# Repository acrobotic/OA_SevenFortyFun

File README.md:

## Ai\_Synth\_AVR

PCB design files (EAGLE) for a transistor-scale version of the μA741 Op-Amp
Integrated Circuit.

## Description

For more details, check out the product page at:

   * https://acrobotic.com/acr-00003

Designed by ACROBOTIC Industries in collaboration with Shane Petcavich.  
Please consider buying products from us to help fund future Open-Source 
projects like this! We’ll always put our best effort in every project, and 
release all our design files and code for you to use. 

## License

Released under the Creative Commons Attribution, Share-Alike license. Please 
check LICENSE.txt for more information. All text above must be included in any 
redistribution.

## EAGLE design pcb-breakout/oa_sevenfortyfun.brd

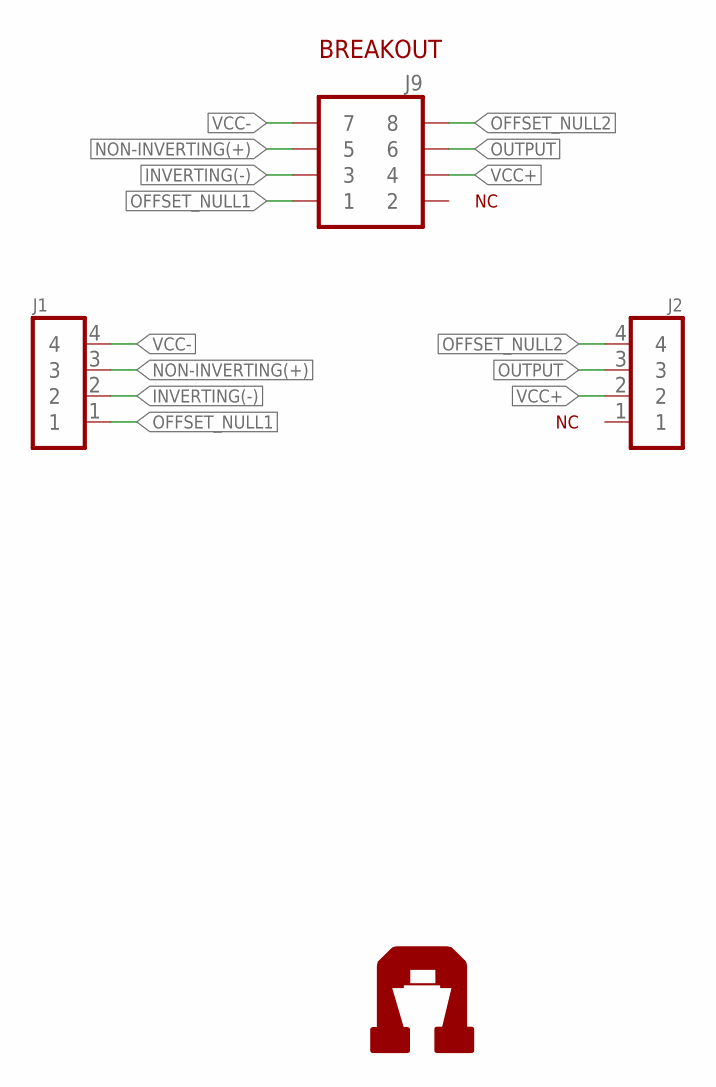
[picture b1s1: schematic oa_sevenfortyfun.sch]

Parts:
J1: 1X04NOSILK; 1X04-NOSILK
J2: 1X04NOFIRST; 1X04-NOFIRST
J9: 2X04SHR; 2X04-SHR
U$3: AI-LOGOXS; AI-LOGO-XS

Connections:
INVERTING(-): J1.2, J9.3
NON-INVERTING(+): J1.3, J9.5
OFFSET_NULL1: J1.1, J9.1
OFFSET_NULL2: J2.4, J9.8
OUTPUT: J2.3, J9.6
VCC+: J2.2, J9.4
VCC-: J1.4, J9.7

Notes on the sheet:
BREAKOUT

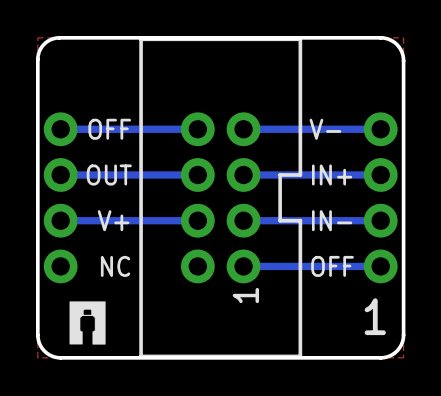
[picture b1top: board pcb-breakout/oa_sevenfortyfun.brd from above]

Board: 2 copper layers, 20.3 x 17.8 mm, 4 parts (0 on the bottom side), 7 nets.

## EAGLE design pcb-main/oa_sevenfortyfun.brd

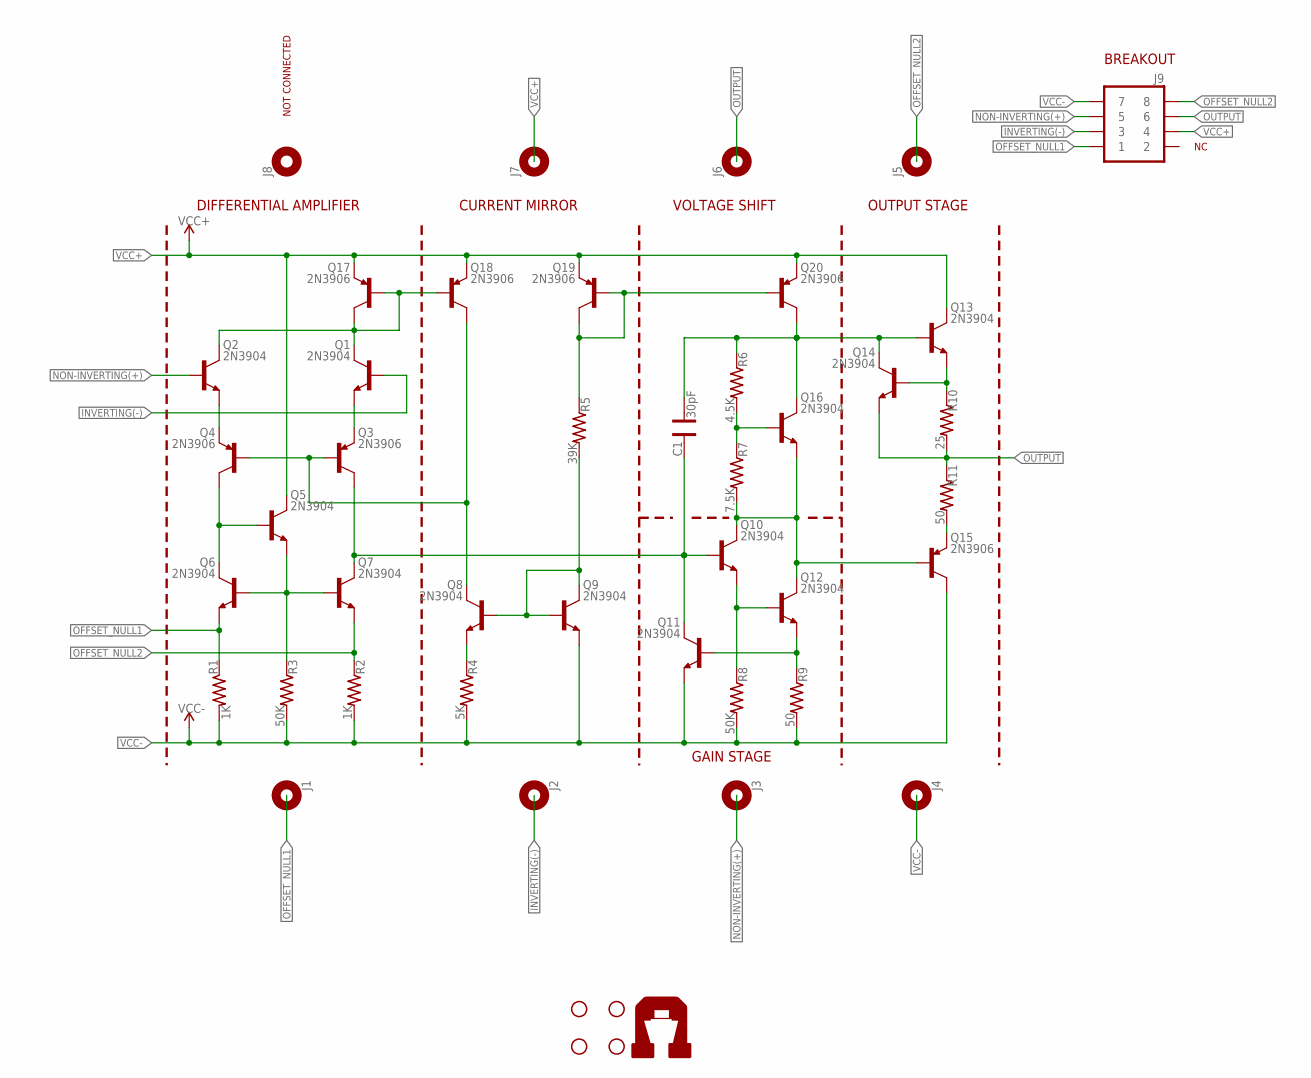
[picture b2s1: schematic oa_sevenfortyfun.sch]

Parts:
C1: 30pF; CAP-025X050
J1, J2, J3, J4, J5, J6, J7, J8: 1X01-TERM
J9: 2X04SHR; 2X04-SHR
Q1, Q2, Q5, Q6, Q7, Q8, Q9, Q10, Q11, Q12, Q13, Q14, Q16: 2N3904; TO-92-NPN
Q3, Q4, Q15, Q17, Q18, Q19, Q20: 2N3906; TO-92-PNP
R1, R2: 1K; RES-AXIAL-0.4
R3, R8: 50K; RES-AXIAL-0.4
R4: 5K; RES-AXIAL-0.4
R5: 39K; RES-AXIAL-0.4
R6: 4.5K; RES-AXIAL-0.4
R7: 7.5K; RES-AXIAL-0.4
R9, R11: 50; RES-AXIAL-0.4
R10: 25; RES-AXIAL-0.4
STANDOFF1, STANDOFF2, STANDOFF3, STANDOFF4: STAND-OFF4; STAND-OFF-4
U$3: AI-LOGOL; AI-LOGO-L

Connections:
INVERTING(-): J2.1, J9.3, Q1.2 (B)
unnamed: Q1.3 (C), Q2.3 (C), Q17.1 (C), Q17.2 (B), Q18.2 (B)
unnamed: Q2.1 (E), Q4.3 (E)
unnamed: Q1.1 (E), Q3.3 (E)
unnamed: Q4.1 (C), Q5.2 (B), Q6.3 (C)
unnamed: C1.2, Q3.1 (C), Q7.3 (C), Q10.2 (B), Q11.3 (C)
unnamed: Q5.1 (E), Q6.2 (B), Q7.2 (B), R3.P$1 (1)
unnamed: Q15.3 (E), R11.P$2 (2)
unnamed: Q3.2 (B), Q4.2 (B), Q8.3 (C), Q18.1 (C)
unnamed: Q8.1 (E), R4.P$1 (1)
unnamed: Q10.1 (E), Q12.2 (B), R8.P$1 (1)
unnamed: Q19.1 (C), Q19.2 (B), Q20.2 (B), R5.P$1 (1)
unnamed: Q8.2 (B), Q9.2 (B), Q9.3 (C), R5.P$2 (2)
unnamed: Q10.3 (C), Q12.3 (C), Q15.2 (B), Q16.1 (E), R7.P$2 (2)
unnamed: Q16.2 (B), R6.P$2 (2), R7.P$1 (1)
unnamed: Q11.2 (B), Q12.1 (E), R9.P$1 (1)
unnamed: C1.1, Q13.2 (B), Q14.3 (C), Q16.3 (C), Q20.1 (C), R6.P$1 (1)
unnamed: Q13.1 (E), Q14.2 (B), R10.P$1 (1)
NON-INVERTING(+): J3.1, J9.5, Q2.2 (B)
OFFSET_NULL1: J1.1, J9.1, Q6.1 (E), R1.P$1 (1)
OFFSET_NULL2: J5.1, J9.8, Q7.1 (E), R2.P$1 (1)
OUTPUT: J6.1, J9.6, Q14.1 (E), R10.P$2 (2), R11.P$1 (1)
VCC+: J7.1, J9.4, Q5.3 (C), Q13.3 (C), Q17.3 (E), Q18.3 (E), Q19.3 (E), Q20.3 (E)
VCC-: J4.1, J9.7, Q9.1 (E), Q11.1 (E), Q15.1 (C), R1.P$2 (2), R2.P$2 (2), R3.P$2 (2), R4.P$2 (2), R8.P$2 (2), R9.P$2 (2)

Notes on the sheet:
DIFFERENTIAL AMPLIFIER
CURRENT MIRROR
VOLTAGE SHIFT
OUTPUT STAGE
BREAKOUT
NOT CONNECTED
GAIN STAGE

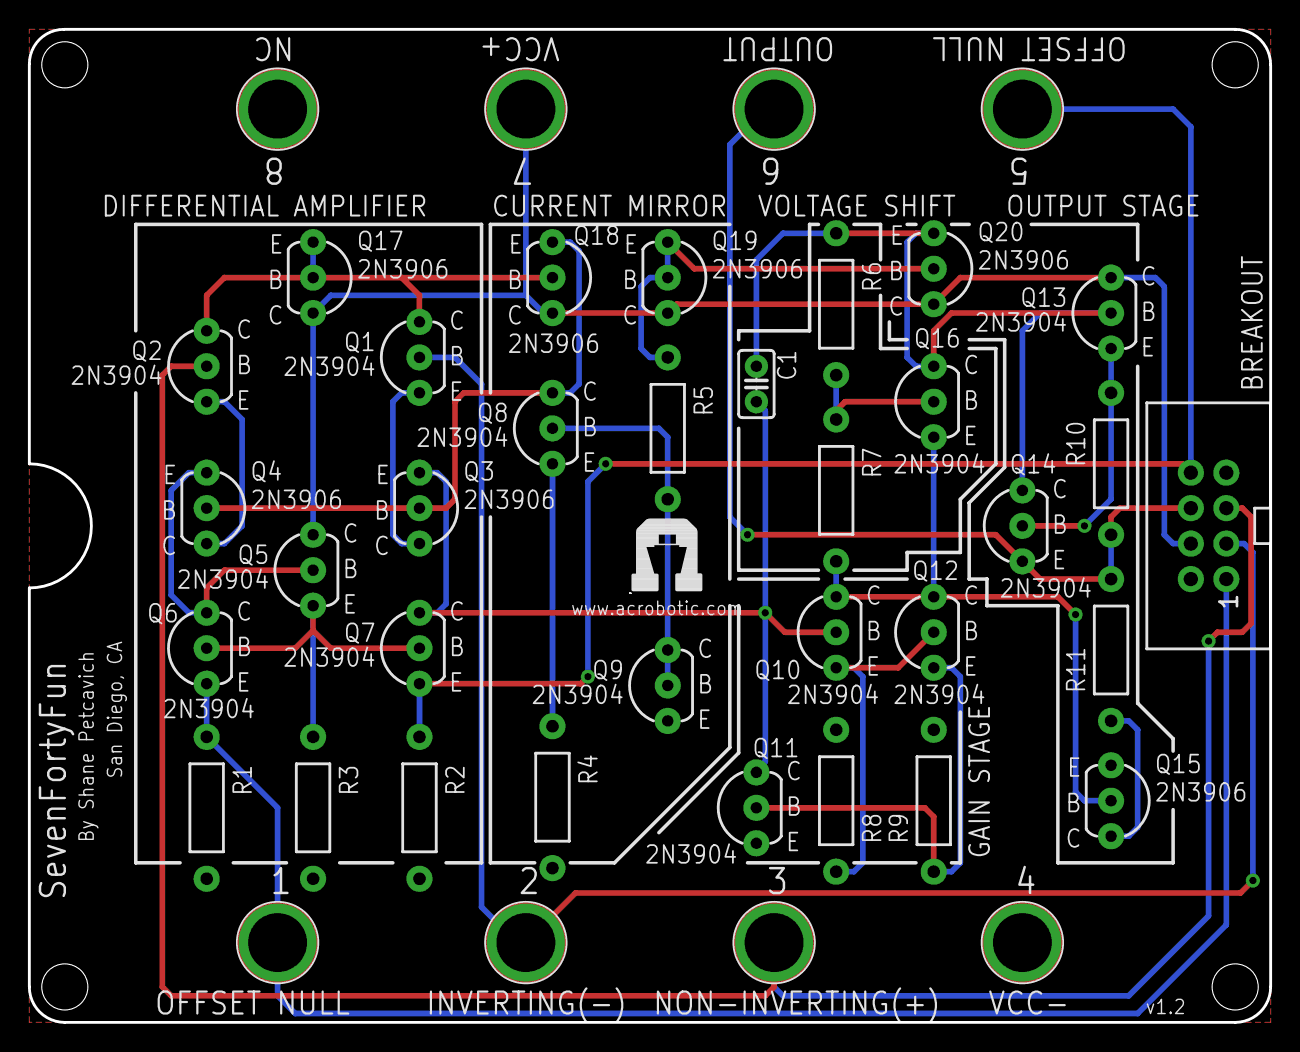
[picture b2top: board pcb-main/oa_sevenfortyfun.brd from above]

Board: 2 copper layers, 88.9 x 71.1 mm, 46 parts (0 on the bottom side), 24 nets.

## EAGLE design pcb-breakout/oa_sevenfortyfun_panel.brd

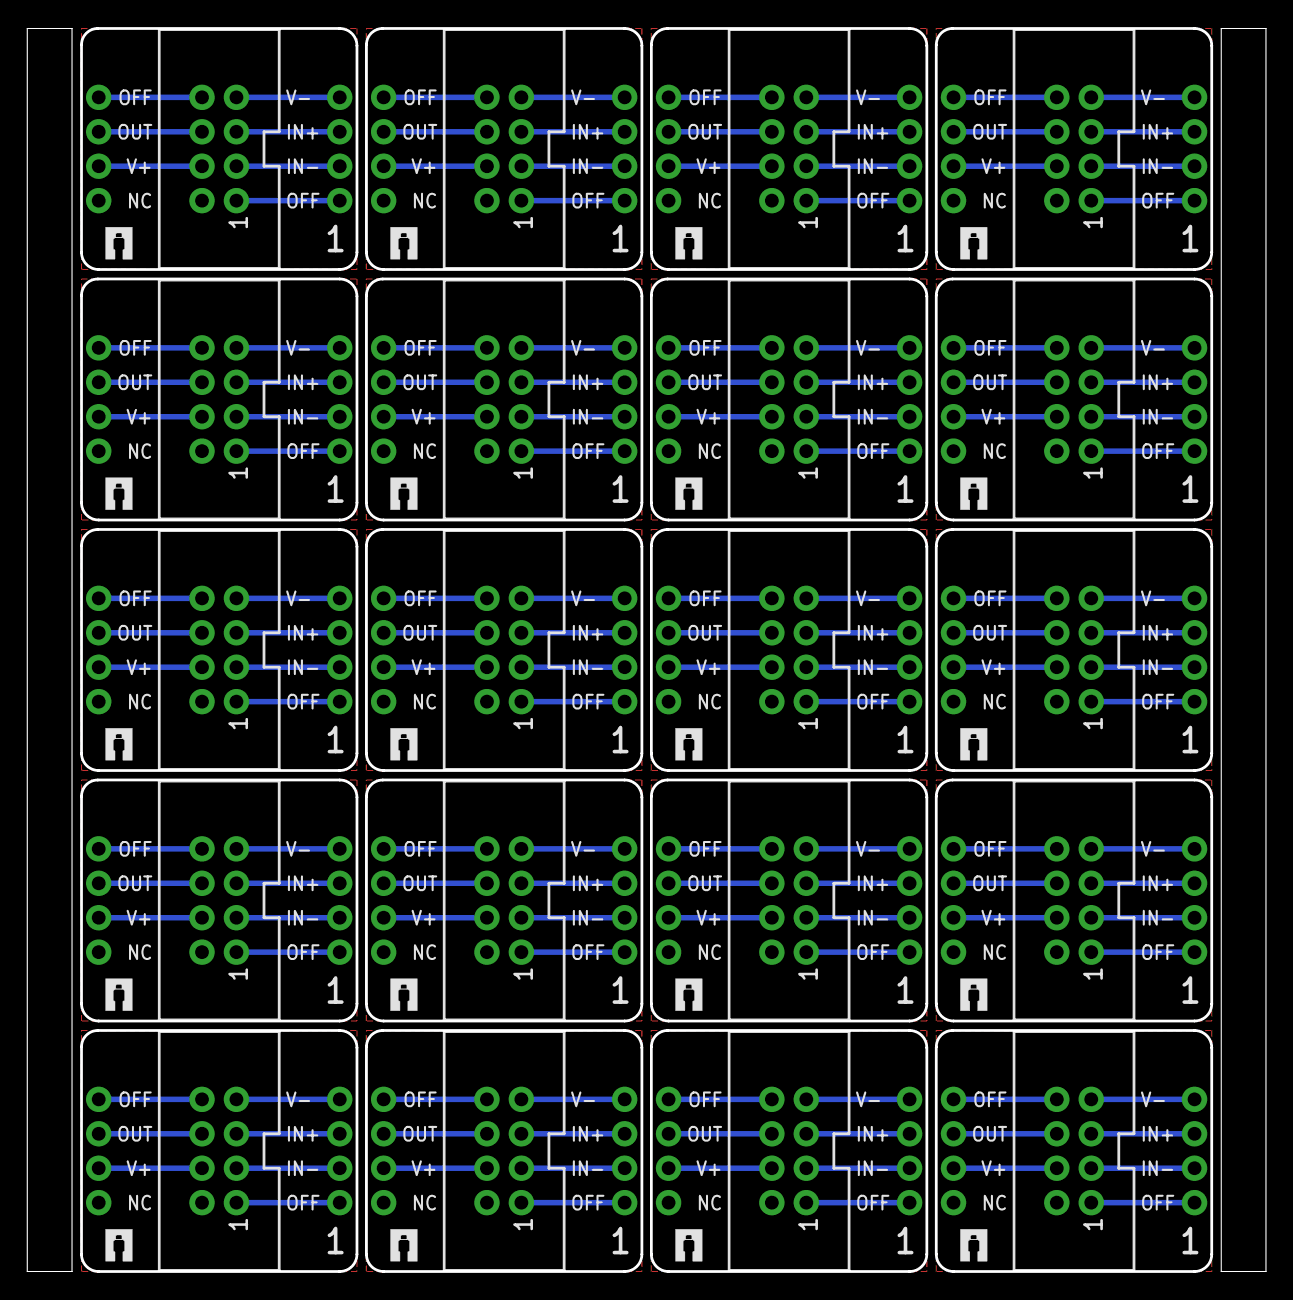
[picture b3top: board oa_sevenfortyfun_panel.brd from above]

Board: 2 copper layers, 91.2 x 91.7 mm, 80 parts (0 on the bottom side), 140 nets.

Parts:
J1, J4, J7, J11, J14, J17, J20, J23, J26, J29, J32, J35, J38, J41, J44, J47, J50, J53, J56, J59: 1X04NOSILK; 1X04-NOSILK
J2, J5, J8, J12, J15, J18, J21, J24, J27, J30, J33, J36, J39, J42, J45, J48, J51, J54, J57, J60: 1X04NOFIRST; 1X04-NOFIRST
J3, J6, J9, J10, J13, J16, J19, J22, J25, J28, J31, J34, J37, J40, J43, J46, J49, J52, J55, J58: 2X04SHR; 2X04-SHR
U$1, U$2, U$3, U$4, U$5, U$6, U$7, U$8, U$9, U$10, U$11, U$12, U$13, U$14, U$15, U$16, U$17, U$18, U$19, U$20: AI-LOGOXS; AI-LOGO-XS

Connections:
INVERTING(-): J1.2, J9.3
INVERTING(-)1: J3.3, J4.2
INVERTING(-)2: J6.3, J7.2
INVERTING(-)3: J10.3, J11.2
INVERTING(-)4: J13.3, J14.2
INVERTING(-)5: J16.3, J17.2
INVERTING(-)6: J19.3, J20.2
INVERTING(-)7: J22.3, J23.2
INVERTING(-)8: J25.3, J26.2
INVERTING(-)9: J28.3, J29.2
INVERTING(-)10: J31.3, J32.2
INVERTING(-)11: J34.3, J35.2
INVERTING(-)12: J37.3, J38.2
INVERTING(-)13: J40.3, J41.2
INVERTING(-)14: J43.3, J44.2
INVERTING(-)15: J46.3, J47.2
INVERTING(-)16: J49.3, J50.2
INVERTING(-)17: J52.3, J53.2
INVERTING(-)18: J55.3, J56.2
INVERTING(-)19: J58.3, J59.2
NON-INVERTING(+): J1.3, J9.5
NON-INVERTING(+)1: J3.5, J4.3
NON-INVERTING(+)2: J6.5, J7.3
NON-INVERTING(+)3: J10.5, J11.3
NON-INVERTING(+)4: J13.5, J14.3
NON-INVERTING(+)5: J16.5, J17.3
NON-INVERTING(+)6: J19.5, J20.3
NON-INVERTING(+)7: J22.5, J23.3
NON-INVERTING(+)8: J25.5, J26.3
NON-INVERTING(+)9: J28.5, J29.3
NON-INVERTING(+)10: J31.5, J32.3
NON-INVERTING(+)11: J34.5, J35.3
NON-INVERTING(+)12: J37.5, J38.3
NON-INVERTING(+)13: J40.5, J41.3
NON-INVERTING(+)14: J43.5, J44.3
NON-INVERTING(+)15: J46.5, J47.3
NON-INVERTING(+)16: J49.5, J50.3
NON-INVERTING(+)17: J52.5, J53.3
NON-INVERTING(+)18: J55.5, J56.3
NON-INVERTING(+)19: J58.5, J59.3
OFFSET_NULL1: J1.1, J9.1
OFFSET_NULL2: J2.4, J9.8
OFFSET_NULL3: J3.8, J5.4
OFFSET_NULL4: J3.1, J4.1
OFFSET_NULL5: J6.8, J8.4
OFFSET_NULL6: J6.1, J7.1
OFFSET_NULL7: J10.8, J12.4
OFFSET_NULL8: J10.1, J11.1
OFFSET_NULL9: J13.8, J15.4
OFFSET_NULL10: J13.1, J14.1
OFFSET_NULL11: J16.8, J18.4
OFFSET_NULL12: J16.1, J17.1
OFFSET_NULL13: J19.8, J21.4
OFFSET_NULL14: J19.1, J20.1
OFFSET_NULL15: J22.8, J24.4
OFFSET_NULL16: J22.1, J23.1
OFFSET_NULL17: J25.8, J27.4
OFFSET_NULL18: J25.1, J26.1
OFFSET_NULL19: J28.8, J30.4
OFFSET_NULL20: J28.1, J29.1
OFFSET_NULL21: J31.8, J33.4
OFFSET_NULL22: J31.1, J32.1
OFFSET_NULL23: J34.8, J36.4
OFFSET_NULL24: J34.1, J35.1
OFFSET_NULL25: J37.8, J39.4
OFFSET_NULL26: J37.1, J38.1
OFFSET_NULL27: J40.8, J42.4
OFFSET_NULL28: J40.1, J41.1
OFFSET_NULL29: J43.8, J45.4
OFFSET_NULL30: J43.1, J44.1
OFFSET_NULL31: J46.8, J48.4
OFFSET_NULL32: J46.1, J47.1
OFFSET_NULL33: J49.8, J51.4
OFFSET_NULL34: J49.1, J50.1
OFFSET_NULL35: J52.8, J54.4
OFFSET_NULL36: J52.1, J53.1
OFFSET_NULL37: J55.8, J57.4
OFFSET_NULL38: J55.1, J56.1
OFFSET_NULL39: J58.8, J60.4
OFFSET_NULL40: J58.1, J59.1
OUTPUT: J2.3, J9.6
OUTPUT1: J3.6, J5.3
OUTPUT2: J6.6, J8.3
OUTPUT3: J10.6, J12.3
OUTPUT4: J13.6, J15.3
OUTPUT5: J16.6, J18.3
OUTPUT6: J19.6, J21.3
OUTPUT7: J22.6, J24.3
OUTPUT8: J25.6, J27.3
OUTPUT9: J28.6, J30.3
OUTPUT10: J31.6, J33.3
OUTPUT11: J34.6, J36.3
OUTPUT12: J37.6, J39.3
OUTPUT13: J40.6, J42.3
OUTPUT14: J43.6, J45.3
OUTPUT15: J46.6, J48.3
OUTPUT16: J49.6, J51.3
OUTPUT17: J52.6, J54.3
OUTPUT18: J55.6, J57.3
OUTPUT19: J58.6, J60.3
VCC+: J2.2, J9.4
VCC+1: J3.4, J5.2
VCC+2: J6.4, J8.2
VCC+3: J10.4, J12.2
VCC+4: J13.4, J15.2
VCC+5: J16.4, J18.2
VCC+6: J19.4, J21.2
VCC+7: J22.4, J24.2
VCC+8: J25.4, J27.2
VCC+9: J28.4, J30.2
VCC+10: J31.4, J33.2
VCC+11: J34.4, J36.2
VCC+12: J37.4, J39.2
VCC+13: J40.4, J42.2
VCC+14: J43.4, J45.2
VCC+15: J46.4, J48.2
VCC+16: J49.4, J51.2
VCC+17: J52.4, J54.2
VCC+18: J55.4, J57.2
VCC+19: J58.4, J60.2
VCC-: J1.4, J9.7
VCC-1: J3.7, J4.4
VCC-2: J6.7, J7.4
VCC-3: J10.7, J11.4
VCC-4: J13.7, J14.4
VCC-5: J16.7, J17.4
VCC-6: J19.7, J20.4
VCC-7: J22.7, J23.4
VCC-8: J25.7, J26.4
VCC-9: J28.7, J29.4
VCC-10: J31.7, J32.4
VCC-11: J34.7, J35.4
VCC-12: J37.7, J38.4
VCC-13: J40.7, J41.4
VCC-14: J43.7, J44.4
VCC-15: J46.7, J47.4
VCC-16: J49.7, J50.4
VCC-17: J52.7, J53.4
VCC-18: J55.7, J56.4
VCC-19: J58.7, J59.4

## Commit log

2014-08-18 updating
2014-08-18 Working on silkscreen
2014-08-19 starting to route
2014-08-19 Routed. Worked on silkscreen.
2014-08-19 added breakout board
2014-08-20 adding gerbers
2014-08-20 matching functional blocks to v1.0
2014-08-21 minor silkscreen change
2014-08-22 updated to EAGLE 7
2014-09-05 adding BOM
2014-09-14 added PCB to BOM
2014-11-27 regenerated gerbers
2014-12-02 updated files
2014-12-02 latest update (silkscreen changes)
2014-12-02 updated version on schematic
2015-02-26 panelized breakout pcb
2015-10-27 updating guides
